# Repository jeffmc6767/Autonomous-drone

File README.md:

JFC,
-
My custom 20x20 drone FC stack for 4s setups, and my custom 3 inch drone frame. 

**FOR THE STARDANCE REVIEWS:** I submitted this a long time ago I dont remember if I said in the note. In my KICAD schematic the wiring is all on the LEFT side. Just zoom out and you can see everything.
Specs:
- 

- up to 99km/h (I calculated based on other drones with similar setup and weight)
- A theoretical 5-7 minutes of flight time though im not sure 
- Costs around 1.2$ a print and tees 3.5 hours. 
- 4K video 60fps (from the dji o4 air unit)
- Usable with Ardu pilot, betafpv, and most other open source software, though I coded one myself(and with the help of AI). Its under the Firmware file
- 44g PLA and PETG print. 

Build guide:
-

Here's how you can start building this yourself:

1. Produce the PCB(like from a pcb manufacturer)
2. Buy all components from the BOM.CSV.
3. Solder all of the components on the PCB(I would recoment using the PCB file because I deleted a lot of the silkscreen text so it would be easier to design)
4. Follow the instructions in the 'Firmware Readme.md' (In the firmware file)
5. Print the drone frame(More about it below)
6. Install the ESC, motors, and solder the connections.
7. Install the FC and solder those connections and connect the ESC to the FC.
8. Install the DJI o4 air unit and also solder or connect the pins and headers. Mount the camera and antennas.
9. If you prefer ELRS you can install that too. I have included the pins. TX, RX, 5.5V, GND
10. Pair with your DJI Goggles and ELRS or DJI controller
11. FLYYY!!

**About the drone frame:**
I have included 3 step files:
1. 1x Top Plate - Top cover for the frame
2. 1x Bottom Plate - The bottom plate
3. 2x TPU Guards - Protects the propellers and motors

Images gallery:
-

Current Version: 
-
**V5.5:** New Drone frame I designed myself: 

It's a 3 inch drone frame that I designed for 1506 motors. It can support a 20x20mm stack and 25.4x25.4 dji o4 air unit. 

It has 4 rubber/tpu things that go around the bottom of the props to protect it. 

In total, it weighs 44g when 3d printed. 

**V5:**
PCB layout:  
The main changes I made was the dimensions from 39mmx37mm to 30mmx32mm. Everything is now compacted and looks much better from the V3 where it was larger and stuff was everywhere. I improved the routing of all of the components and moved every single component to the top of the board that I can use a hot plate and solder everything at once more easily and efficiently. 

- Added ELRS pads for communication
- Added GPS RX and TX
- Added Borometer pads
- Coded the firmware

**Past Versions:**
V4:
-

transferred all B.CU components to the F.CU (not the JST connector) and modified the Edge.cuts 

V3:
-

V2:
-

V1:
-

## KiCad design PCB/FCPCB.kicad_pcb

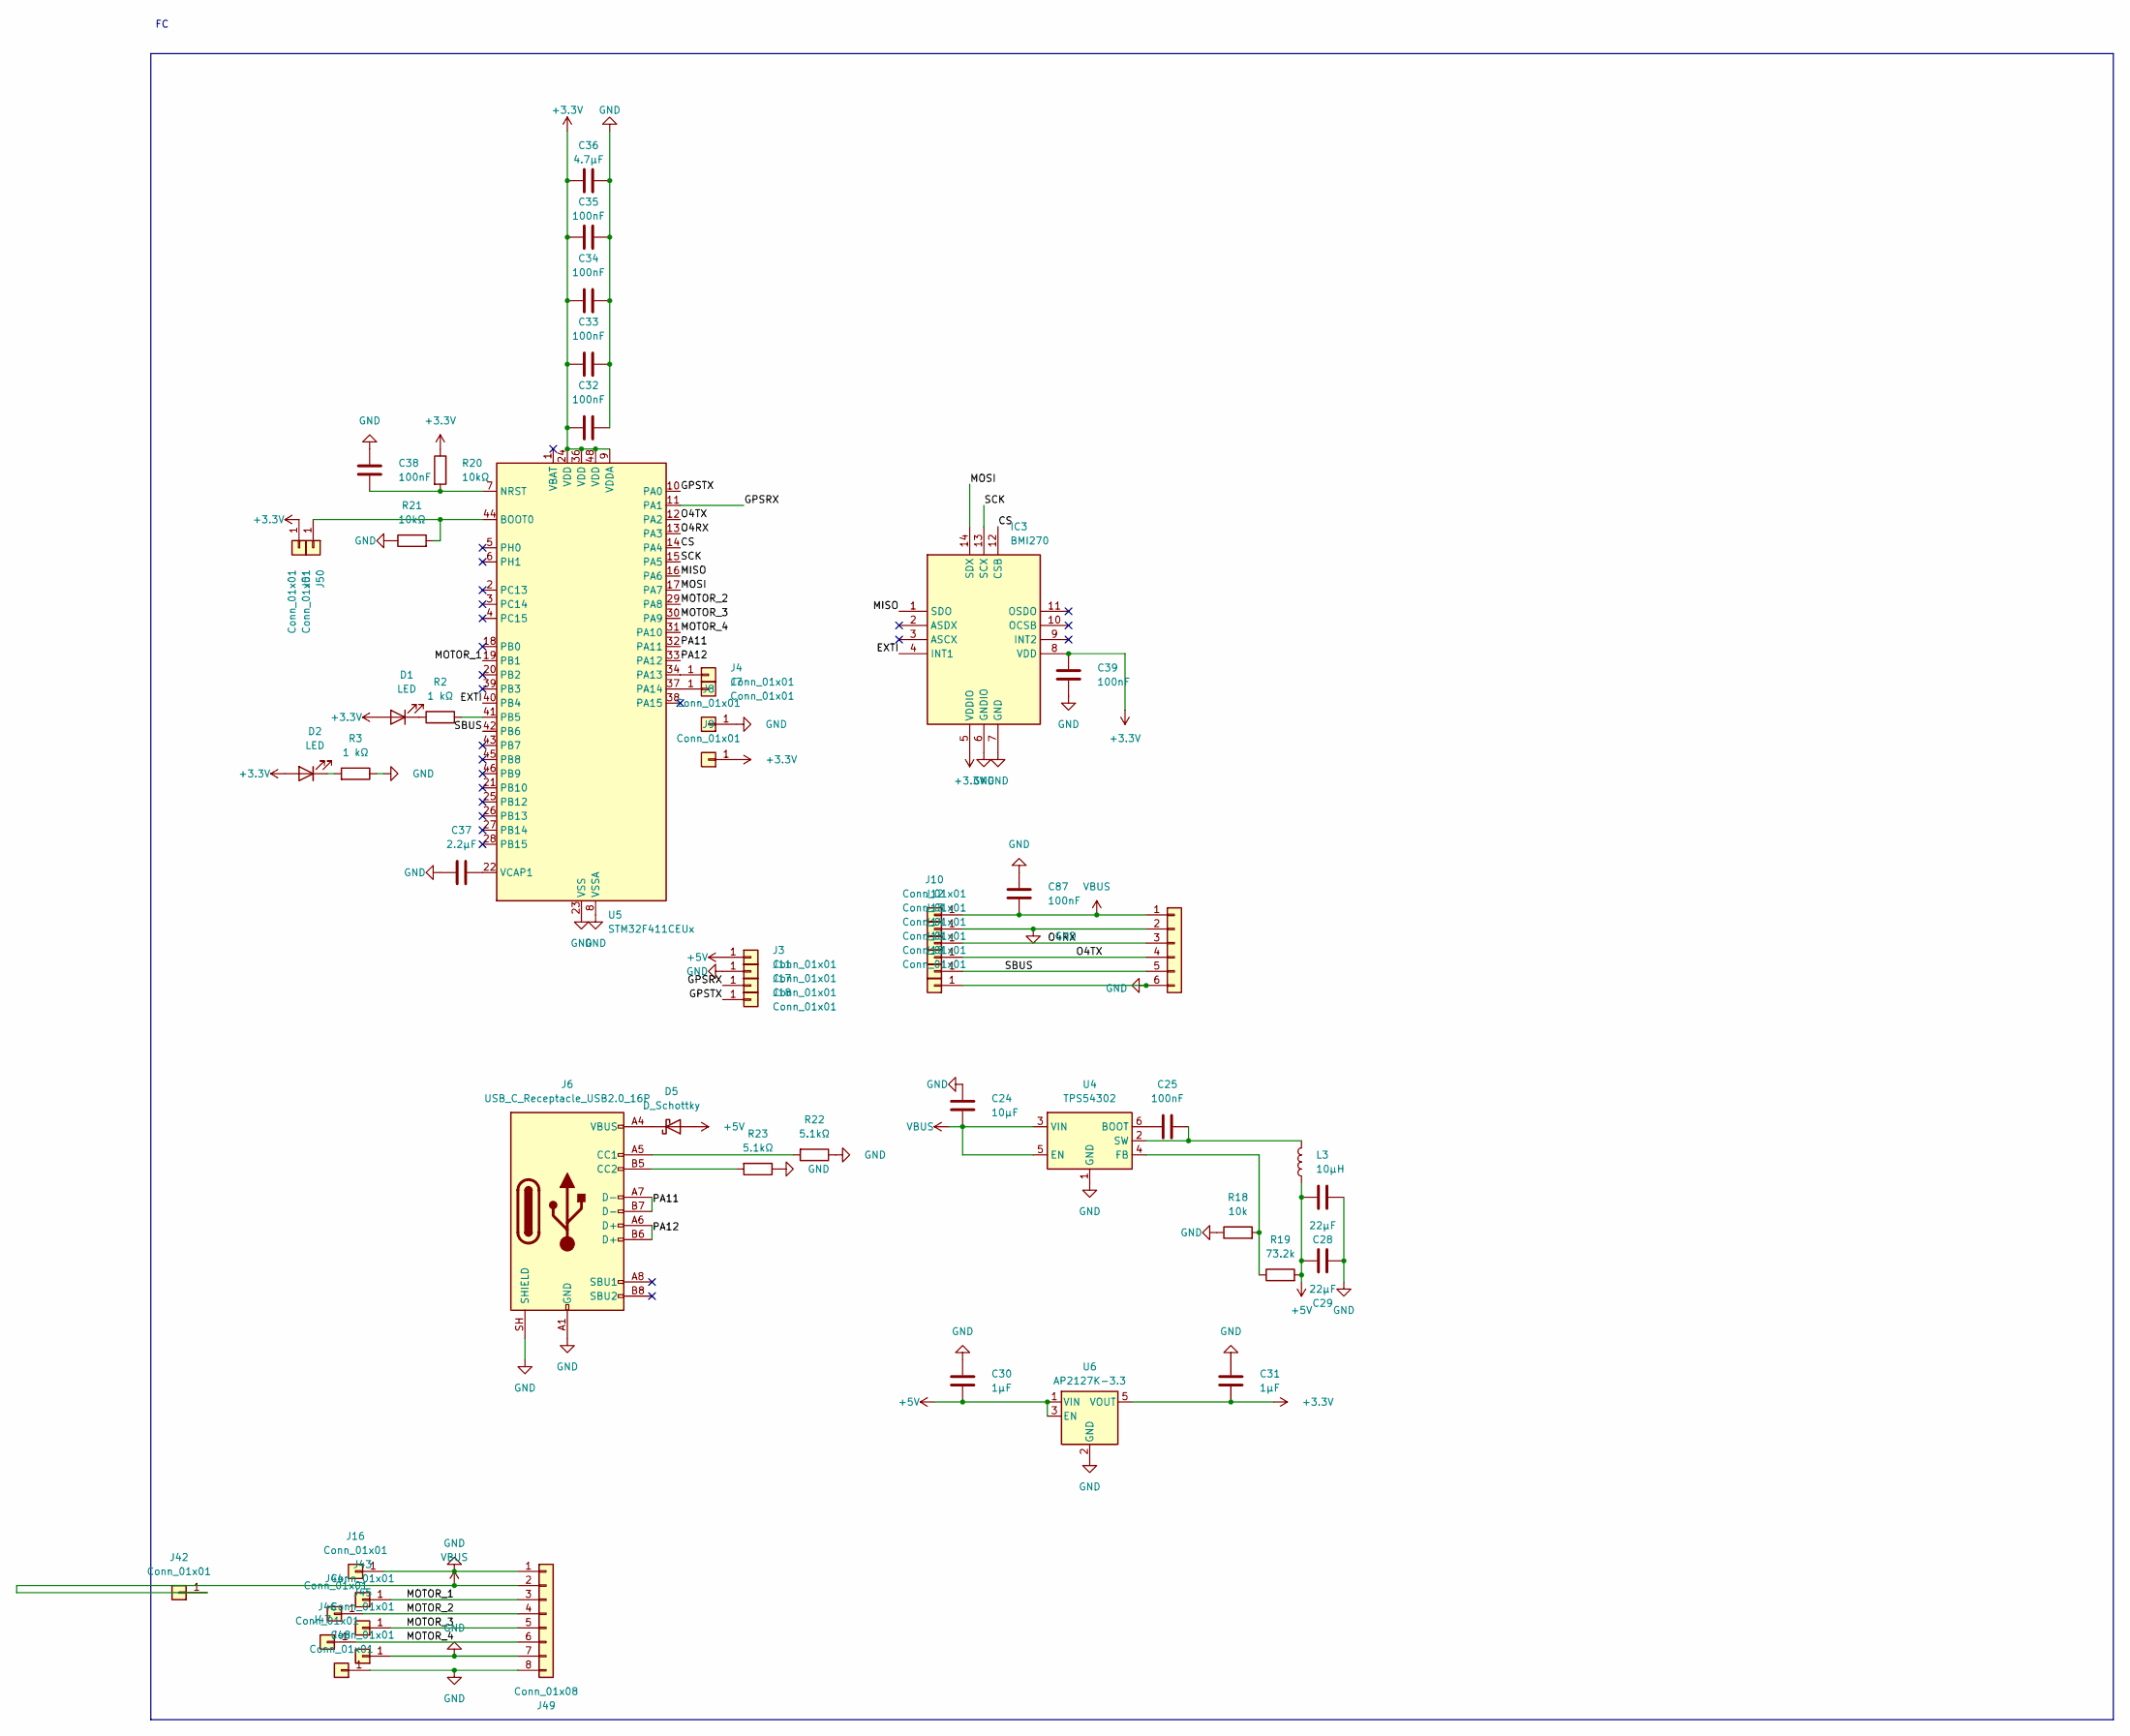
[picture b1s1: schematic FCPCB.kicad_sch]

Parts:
C24: 10µF; C_0402_1005Metric_Pad0.74x0.62mm_HandSolder
C25, C32, C33, C34, C35, C38, C39, C87: 100nF; C_0402_1005Metric_Pad0.74x0.62mm_HandSolder
C28: 22µF; C_0402_1005Metric_Pad0.74x0.62mm_HandSolder
C29: 22µF; C_0805_2012Metric_Pad1.18x1.45mm_HandSolder
C30, C31: 1µF; C_0402_1005Metric_Pad0.74x0.62mm_HandSolder
C36: 4.7µF; C_0402_1005Metric_Pad0.74x0.62mm_HandSolder
C37: 2.2µF; C_0402_1005Metric_Pad0.74x0.62mm_HandSolder
D1, D2: LED; LED_0603_1608Metric_Pad1.05x0.95mm_HandSolder
D5: D_Schottky; D_SOD-123
IC3: BMI270; Manufacturer_Part_Number BMI270; Mouser Part Number 262-BMI270
J3, J4, J7, J8, J9, J10, J11, J12, J13, J14, J15, J16, J17, J18, J19, J42, J43, J44, J45, J46, J47, J48, J50, J51: Conn_01x01; TestPoint_Pad_1.0x1.0mm
J5: Conn_01x06; JST_SH_SM06B-SRSS-TB_1x06-1MP_P1.00mm_Horizontal
J6: USB_C_Receptacle_USB2.0_16P; USB_C_Receptacle_HRO_TYPE-C-31-M-12
J49: Conn_01x08; JST_SH_SM08B-SRSS-TB_1x08-1MP_P1.00mm_Horizontal
L3: 10μH; L_Coilcraft_XAL4020-XXX
R2, R3: 1 kΩ; R_0402_1005Metric_Pad0.72x0.64mm_HandSolder
R18: 10k; R_0402_1005Metric_Pad0.72x0.64mm_HandSolder
R19: 73.2k; R_0402_1005Metric_Pad0.72x0.64mm_HandSolder
R20, R21: 10kΩ; R_0402_1005Metric_Pad0.72x0.64mm_HandSolder
R22, R23: 5.1kΩ; R_0402_1005Metric_Pad0.72x0.64mm_HandSolder
U4: TPS54302; SOT-23-6
U5: STM32F411CEUx; QFN-48-1EP_7x7mm_P0.5mm_EP5.6x5.6mm
U6: AP2127K-3.3; SOT-23-5

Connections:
+3.3V: C31.2, C32.1, C33.1, C34.1, C35.1, C36.1, C39.1, D1.2 (A), D2.2 (A), IC3.5 (VDDIO), IC3.8 (VDD), J9.1 (Pin_1_1), J51.1 (Pin_1_1), R20.1, U5.9 (VDDA), U5.24 (VDD), U5.36 (VDD), U5.48 (VDD), U6.5 (VOUT)
+5V: C28.2, C29.2, C30.2, D5.2 (A), J3.1 (Pin_1_1), L3.1, R19.2, U6.1 (VIN), U6.3 (EN)
/CS: IC3.12 (CSB), U5.14 (PA4)
/EXTI: IC3.4 (INT1), U5.40 (PB4)
/GPSRX: J17.1 (Pin_1_1), U5.11 (PA1)
/GPSTX: J18.1 (Pin_1_1), U5.10 (PA0)
/MISO: IC3.1 (SDO), U5.16 (PA6)
/MOSI: IC3.14 (SDX), U5.17 (PA7)
/MOTOR_1: J43.1 (Pin_1_1), J49.3, U5.19 (PB1)
/MOTOR_2: J44.1 (Pin_1_1), J49.4, U5.29 (PA8)
/MOTOR_3: J45.1 (Pin_1_1), J49.5, U5.30 (PA9)
/MOTOR_4: J46.1 (Pin_1_1), J49.6, U5.31 (PA10)
/O4RX: J5.3, J13.1 (Pin_1_1), U5.13 (PA3)
/O4TX: J5.4, J14.1 (Pin_1_1), U5.12 (PA2)
/PA11: J6.A7 (D-), J6.B7 (D-), U5.32 (PA11)
/PA12: J6.A6 (D+), J6.B6 (D+), U5.33 (PA12)
/SBUS: J5.5, J15.1 (Pin_1_1), U5.42 (PB6)
/SCK: IC3.13 (SCX), U5.15 (PA5)
GND: C24.1, C28.1, C29.1, C30.1, C31.1, C32.2, C33.2, C34.2, C35.2, C36.2, C37.1, C38.1, C39.2, C87.1, IC3.6 (GNDIO), IC3.7 (GND), J5.2, J5.6, J6.A1 (GND), J6.A12 (GND), J6.B1 (GND), J6.B12 (GND), J6.SH (SHIELD), J8.1 (Pin_1_1), J11.1 (Pin_1_1), J12.1 (Pin_1_1), J16.1 (Pin_1_1), J19.1 (Pin_1_1), J47.1 (Pin_1_1), J48.1 (Pin_1_1), J49.1, J49.7, J49.8, R3.1, R18.1, R21.1, R22.1, R23.1, U4.1 (GND), U5.8 (VSSA), U5.23 (VSS), U5.35 (VSS), U5.47 (VSS), U5.49 (VSS), U6.2 (GND)
unnamed: D1.1 (K), R2.1
unnamed: D2.1 (K), R3.2
unnamed: D5.1 (K), J6.A4 (VBUS), J6.A9 (VBUS), J6.B4 (VBUS), J6.B9 (VBUS)
unnamed: J4.1 (Pin_1_1), U5.34 (PA13)
unnamed: J6.A5 (CC1), R22.2
unnamed: J6.B5 (CC2), R23.2
unnamed: J7.1 (Pin_1_1), U5.37 (PA14)
unnamed: J50.1 (Pin_1_1), R21.2, U5.44 (BOOT0)
unnamed: C25.2, U4.6 (BOOT)
unnamed: R18.2, R19.1, U4.4 (FB)
unnamed: C25.1, L3.2, U4.2 (SW)
unnamed: C38.2, R20.2, U5.7 (NRST)
unnamed: R2.2, U5.41 (PB5)
unnamed: C37.2, U5.22 (VCAP1)
VBUS: C24.2, C87.2, J5.1, J10.1 (Pin_1_1), J42.1 (Pin_1_1), J49.2, U4.3 (VIN), U4.5 (EN)

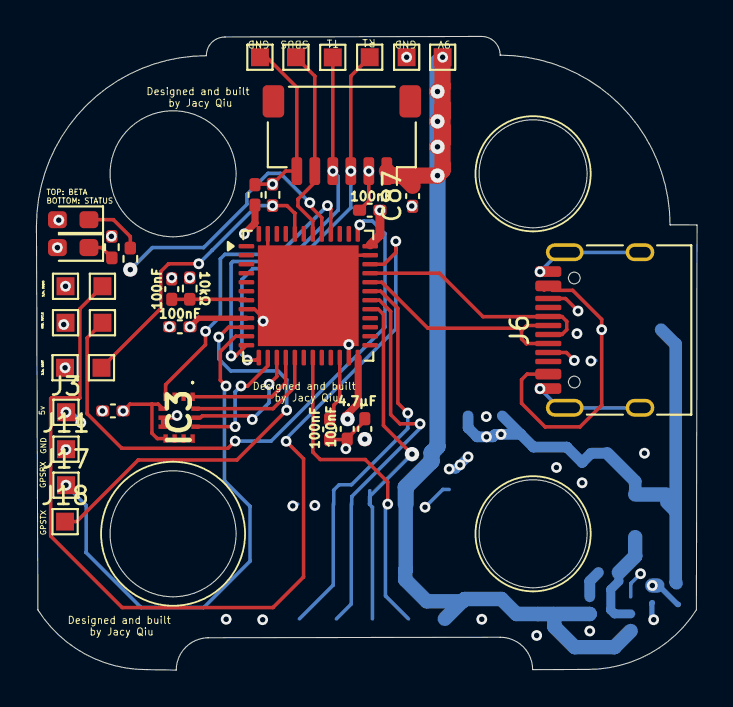
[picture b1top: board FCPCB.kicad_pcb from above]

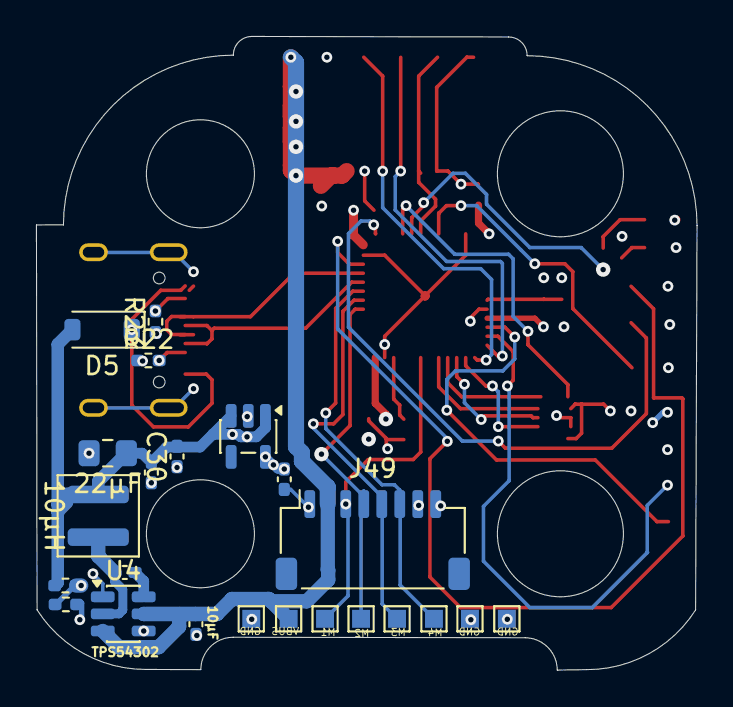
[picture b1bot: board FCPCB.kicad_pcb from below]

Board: 4 copper layers, 36.7 x 35.2 mm, 58 parts (23 on the bottom side), 34 nets.
